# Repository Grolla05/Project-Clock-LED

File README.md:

# ⏱️ Project Clock LED — Digital Clock with Logic Circuits

> A fully functional digital clock built **without programming**, using only digital logic and discrete electronics.

---

## 🧩 What is DigitalClock?

**DigitalClock** is a project developed with the goal of creating a **complete digital clock** capable of accurately counting hours, minutes, and seconds using **only discrete electronic components and digital logic circuits**, **without any programming languages or microcontrollers**.

The project was designed to practically apply knowledge acquired in **Electronics** and **Digital Circuits** courses, resulting in a system capable of operating continuously and stably, displaying the time in real-time on **seven-segment LED displays**.

---

## 🎯 Project Objectives

- ⚡ Design and implement a **rectifier power supply** with proper filtering to power the digital circuits  
- ⏳ Develop a **clock generation system** using **delay and frequency divider circuits**  
- 🔁 Create **synchronous and asynchronous counters** using D flip-flops to count seconds, minutes, and hours  
- 🔢 Integrate **binary to 7-segment decoders** with the counters to correctly display the time values  

---

## ⚙️ Features

✔️ Accurate time counting (hours, minutes, and seconds)  
✔️ Continuous and stable real-time operation  
✔️ Real-time updates on seven-segment displays  
✔️ Fully built with discrete digital logic components  
✔️ No programming or microcontrollers involved  
✔️ Educational project focused on fundamental electronics

---

## 🛠️ Components and Technologies

- **D-type Flip-Flops**  
- **Synchronous/Asynchronous Counters**
- **Pulse Generator (CLOCK)** 
- **Frequency Dividers**  
- **BCD to 7-Segment Decoders**  
- **7-Segment LED Displays**
- **Diode LED's**
- **Rectifier Power Supply with Filter Capacitors**  
- **Logic Gates (AND, NOT, etc...)**

---

## ✨ System Demonstration

 <br>

---

## 👥 Author's

Developed by:

- **Felipe Grolla Freitas** – Control and Automation Engineering Student (PUC-Campinas)
- **Guilherme Oliveira Nogueira** - Control and Automation Engineering Student (PUC-Campinas)
- **Giovanna Lima Salvagnini** - Control and Automation Engineering Student (PUC-Campinas)
- **Henrique Spadaccia Chambó** - Control and Automation Engineering Student (PUC-Campinas)

---

## 💬 Contributions and Learning

This project demonstrated how to build a fully functional digital system using only the fundamentals of sequential and combinational logic.  
It reinforced practical understanding of counters, timing, clock generation, and display interfacing without any programming.

---

> 🧠 *"Digital logic can build time — one pulse at a time."*

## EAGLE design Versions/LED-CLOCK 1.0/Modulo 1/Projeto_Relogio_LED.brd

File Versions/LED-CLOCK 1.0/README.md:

## First version of the project (CLOCK LED with only analog and logic circuit)

## First version of the project in proteus

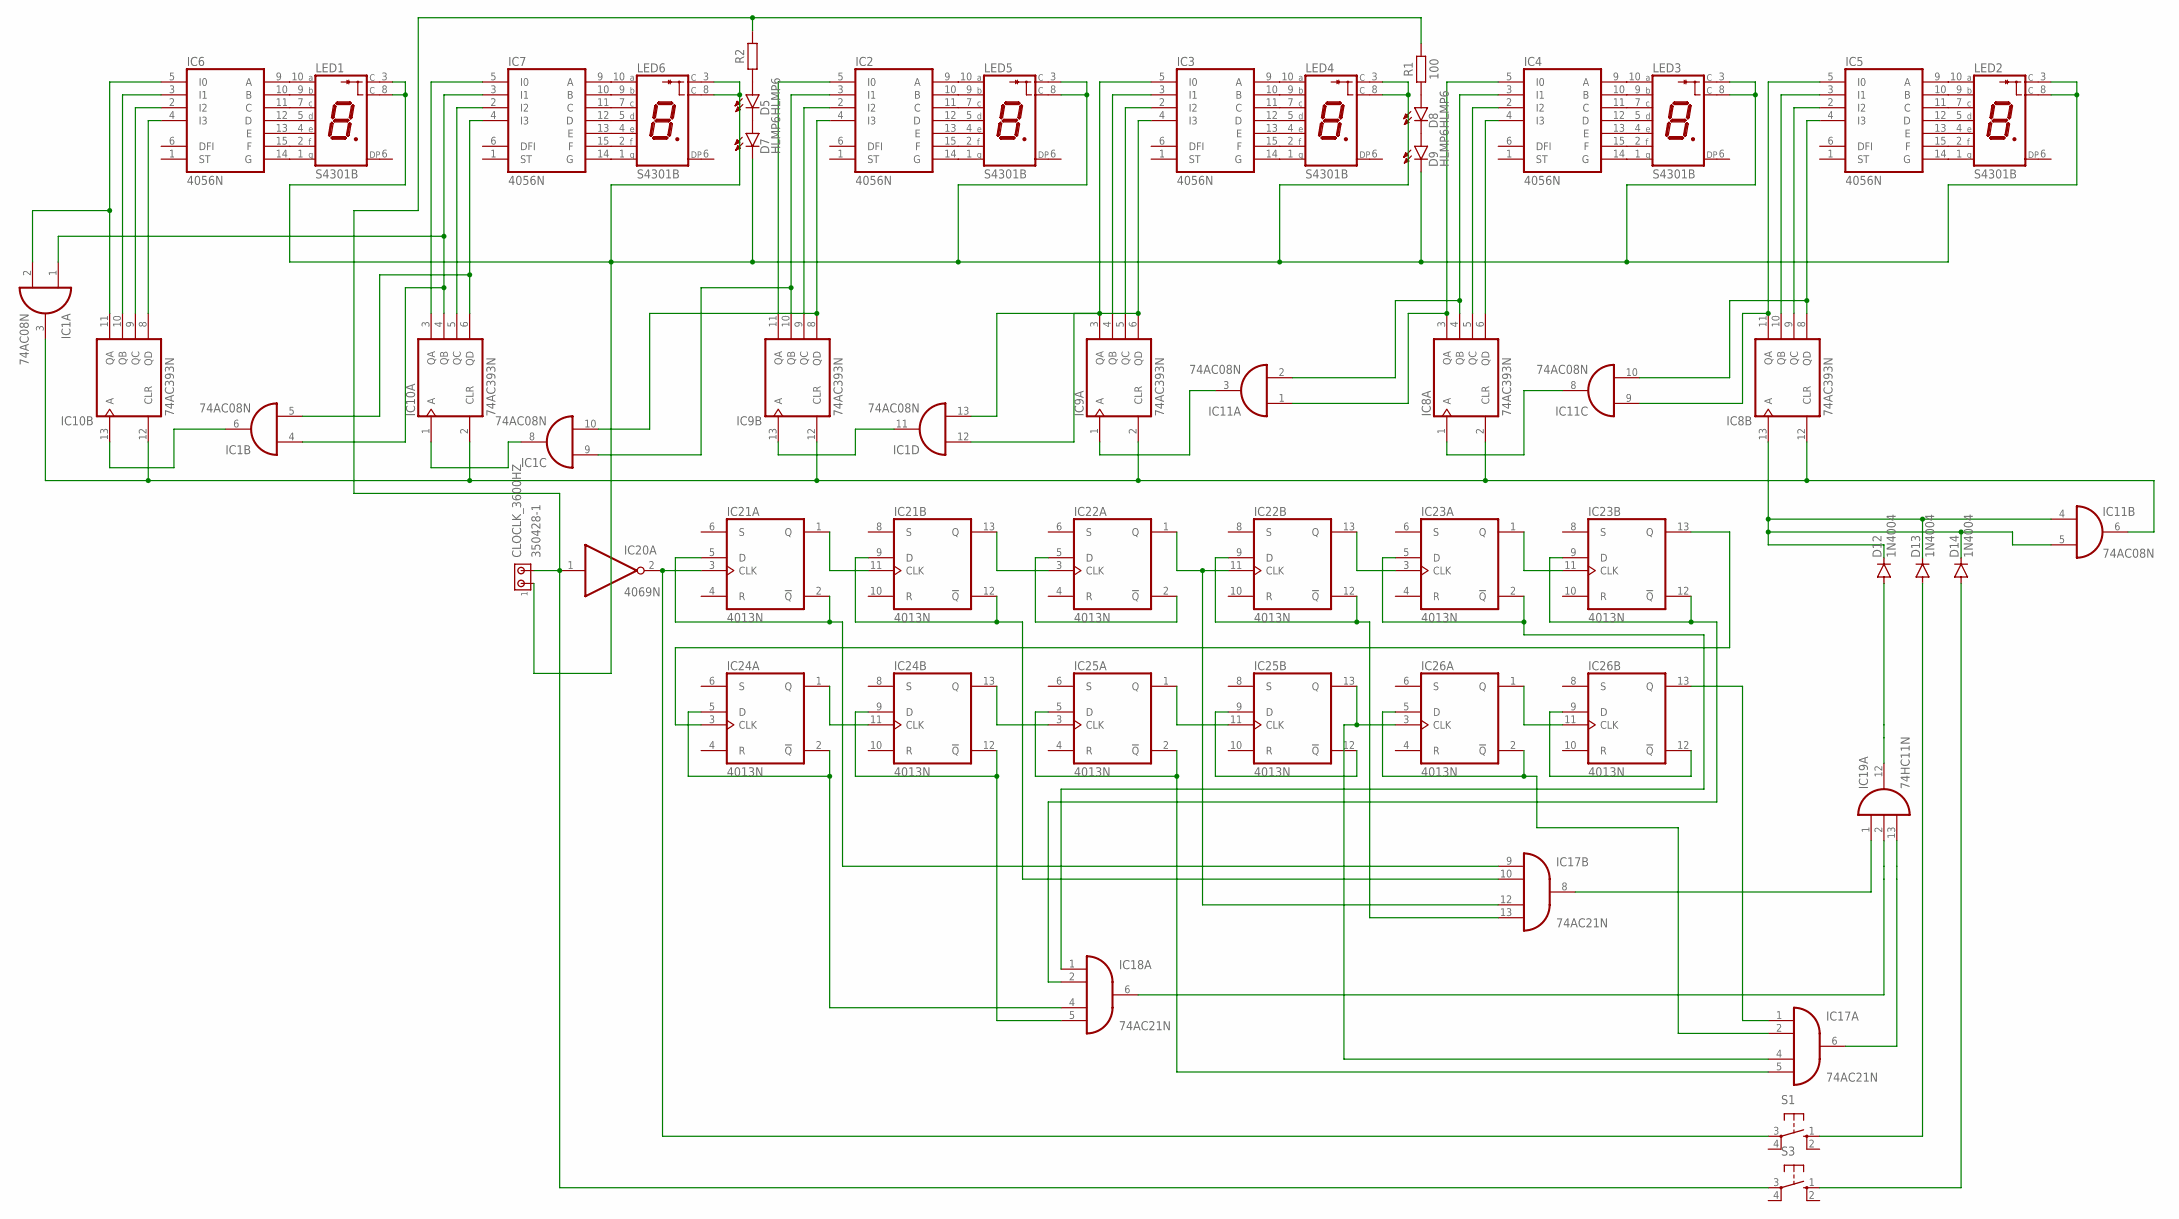
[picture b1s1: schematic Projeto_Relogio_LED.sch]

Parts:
CLOCLK_3600HZ: 350428-1
D5, D7, D8, D9: HLMP6
D12, D13, D14: 1N4004; DO41-10
IC1, IC11: 74AC08N; DIL14
IC2, IC3, IC4, IC5, IC6, IC7: 4056N; DIL16
IC8, IC9, IC10: 74AC393N; DIL14
IC17, IC18: 74AC21N; DIL14
IC19: 74HC11N; DIL14
IC20: 4069N; DIL14
IC21, IC22, IC23, IC24, IC25, IC26: 4013N; DIL14
LED1, LED2, LED3, LED4, LED5, LED6: S4301B
R1, R2: 100; RESAD1016W63L850D250B
S1, S3: 10-XX; B3F-10XX

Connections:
GND: IC1.7 (GND), IC2.8 (GND), IC3.8 (GND), IC4.8 (GND), IC5.8 (GND), IC6.8 (GND), IC7.8 (GND), IC8.7 (GND), IC9.7 (GND), IC10.7 (GND), IC11.7 (GND), IC17.7 (GND), IC18.7 (GND), IC19.7 (GND)
unnamed: IC1.8 (O), IC10.1 (A)
unnamed: IC5.4 (I3), IC8.8 (QD), IC11.10 (I1)
unnamed: IC8.1 (A), IC11.8 (O)
unnamed: D5.A, R2.1
unnamed: D8.A, R1.1
unnamed: D12.A, IC19.12 (O)
unnamed: IC20.2 (O), IC21.3 (CLK), S1.3
unnamed: IC21.1 (Q), IC21.11 (CLK)
unnamed: CLOCLK_3600HZ.2, IC20.1 (I), R1.2, R2.2, S3.3
unnamed: IC21.13 (Q), IC22.3 (CLK)
unnamed: IC17.12 (I2), IC22.1 (Q), IC22.11 (CLK)
unnamed: IC22.13 (Q), IC23.3 (CLK)
unnamed: IC23.1 (Q), IC23.11 (CLK)
unnamed: IC24.1 (Q), IC24.11 (CLK)
unnamed: IC18.4 (I2), IC24.2 (!Q), IC24.5 (D)
unnamed: IC24.13 (Q), IC25.3 (CLK)
unnamed: IC25.1 (Q), IC25.11 (CLK)
unnamed: IC17.4 (I2), IC25.13 (Q), IC26.3 (CLK)
unnamed: IC26.1 (Q), IC26.11 (CLK)
unnamed: IC23.13 (Q), IC24.3 (CLK)
unnamed: IC7.14 (G), LED6.1 (G)
unnamed: IC7.15 (F), LED6.2 (F)
unnamed: IC7.13 (E), LED6.4 (E)
unnamed: IC7.12 (D), LED6.5 (D)
unnamed: IC7.11 (C), LED6.7 (C)
unnamed: IC7.10 (B), LED6.9 (B)
unnamed: IC7.9 (A), LED6.10 (A)
unnamed: IC6.9 (A), LED1.10 (A)
unnamed: IC6.10 (B), LED1.9 (B)
unnamed: IC6.11 (C), LED1.7 (C)
unnamed: IC6.12 (D), LED1.5 (D)
unnamed: IC6.13 (E), LED1.4 (E)
unnamed: IC6.15 (F), LED1.2 (F)
unnamed: IC6.14 (G), LED1.1 (G)
unnamed: IC2.14 (G), LED5.1 (G)
unnamed: IC2.15 (F), LED5.2 (F)
unnamed: IC2.13 (E), LED5.4 (E)
unnamed: IC2.12 (D), LED5.5 (D)
unnamed: IC2.11 (C), LED5.7 (C)
unnamed: IC2.10 (B), LED5.9 (B)
unnamed: IC2.9 (A), LED5.10 (A)
unnamed: IC3.9 (A), LED4.10 (A)
unnamed: IC3.10 (B), LED4.9 (B)
unnamed: IC3.11 (C), LED4.7 (C)
unnamed: IC3.12 (D), LED4.5 (D)
unnamed: IC3.13 (E), LED4.4 (E)
unnamed: IC3.15 (F), LED4.2 (F)
unnamed: IC3.14 (G), LED4.1 (G)
unnamed: IC4.14 (G), LED3.1 (G)
unnamed: IC4.15 (F), LED3.2 (F)
unnamed: IC4.13 (E), LED3.4 (E)
unnamed: IC4.12 (D), LED3.5 (D)
unnamed: IC4.11 (C), LED3.7 (C)
unnamed: IC4.10 (B), LED3.9 (B)
unnamed: IC4.9 (A), LED3.10 (A)
unnamed: IC5.14 (G), LED2.1 (G)
unnamed: IC5.15 (F), LED2.2 (F)
unnamed: IC5.13 (E), LED2.4 (E)
unnamed: IC5.12 (D), LED2.5 (D)
unnamed: IC5.11 (C), LED2.7 (C)
unnamed: IC5.10 (B), LED2.9 (B)
unnamed: IC5.9 (A), LED2.10 (A)
unnamed: IC4.4 (I3), IC8.6 (QD)
unnamed: IC4.2 (I2), IC8.5 (QC)
unnamed: IC4.3 (I1), IC8.4 (QB), IC11.2 (I1)
unnamed: IC4.5 (I0), IC8.3 (QA), IC11.1 (I0)
unnamed: IC5.2 (I2), IC8.9 (QC)
unnamed: IC5.3 (I1), IC8.10 (QB)
unnamed: IC5.5 (I0), IC8.11 (QA), IC11.9 (I0)
unnamed: IC1.13 (I1), IC3.4 (I3), IC9.6 (QD)
unnamed: IC3.2 (I2), IC9.5 (QC)
unnamed: IC3.3 (I1), IC9.4 (QB)
unnamed: IC1.12 (I0), IC3.5 (I0), IC9.3 (QA)
unnamed: IC1.10 (I1), IC2.4 (I3), IC9.8 (QD)
unnamed: IC2.2 (I2), IC9.9 (QC)
unnamed: IC1.9 (I0), IC2.3 (I1), IC9.10 (QB)
unnamed: IC2.5 (I0), IC9.11 (QA)
unnamed: IC1.5 (I1), IC7.4 (I3), IC10.6 (QD)
unnamed: IC7.2 (I2), IC10.5 (QC)
unnamed: IC1.1 (I0), IC1.4 (I0), IC7.3 (I1), IC10.4 (QB)
unnamed: IC7.5 (I0), IC10.3 (QA)
unnamed: IC6.4 (I3), IC10.8 (QD)
unnamed: IC6.2 (I2), IC10.9 (QC)
unnamed: IC6.3 (I1), IC10.10 (QB)
unnamed: IC1.2 (I1), IC6.5 (I0), IC10.11 (QA)
unnamed: D5.K, D7.A
unnamed: D8.K, D9.A
unnamed: IC17.10 (I1), IC21.9 (D), IC21.12 (!Q)
unnamed: IC22.2 (!Q), IC22.5 (D)
unnamed: IC17.13 (I3), IC22.9 (D), IC22.12 (!Q)
unnamed: IC1.6 (O), IC10.13 (A)
unnamed: IC18.1 (I0), IC23.2 (!Q), IC23.5 (D)
unnamed: IC18.2 (I1), IC23.9 (D), IC23.12 (!Q)
unnamed: IC18.5 (I3), IC24.9 (D), IC24.12 (!Q)
unnamed: IC17.5 (I3), IC25.2 (!Q), IC25.5 (D)
unnamed: IC25.9 (D), IC25.12 (!Q)
unnamed: IC26.9 (D), IC26.12 (!Q)
unnamed: IC17.9 (I0), IC21.2 (!Q), IC21.5 (D)
unnamed: D12.C, D13.C, D14.C, IC8.13 (A), IC11.4 (I0), IC11.5 (I1)
unnamed: IC17.8 (O), IC19.1 (I0)
unnamed: D13.A, S1.1 (S)
unnamed: D14.A, S3.1 (S)
unnamed: IC18.6 (O), IC19.2 (I1)
unnamed: IC1.3 (O), IC8.2 (CLR), IC8.12 (CLR), IC9.2 (CLR), IC9.12 (CLR), IC10.2 (CLR), IC10.12 (CLR), IC11.6 (O)
unnamed: IC17.1 (I0), IC26.13 (Q)
unnamed: CLOCLK_3600HZ.1, D7.K, D9.K, LED1.3 (C), LED1.8 (C), LED2.3 (C), LED2.8 (C), LED3.3 (C), LED3.8 (C), LED4.3 (C), LED4.8 (C), LED5.3 (C), LED5.8 (C), LED6.3 (C), LED6.8 (C)
unnamed: IC9.1 (A), IC11.3 (O)
unnamed: IC17.2 (I1), IC26.2 (!Q), IC26.5 (D)
unnamed: IC1.11 (O), IC9.13 (A)
unnamed: IC17.6 (O), IC19.13 (I2)
VCC: IC1.14 (VCC), IC2.16 (VCC), IC3.16 (VCC), IC4.16 (VCC), IC5.16 (VCC), IC6.16 (VCC), IC7.16 (VCC), IC8.14 (VCC), IC9.14 (VCC), IC10.14 (VCC), IC11.14 (VCC), IC17.14 (VCC), IC18.14 (VCC), IC19.14 (VCC)
VDD: IC20.14 (VDD), IC21.14 (VDD), IC22.14 (VDD), IC23.14 (VDD), IC24.14 (VDD), IC25.14 (VDD), IC26.14 (VDD)
VEE: IC2.7 (VEE), IC3.7 (VEE), IC4.7 (VEE), IC5.7 (VEE), IC6.7 (VEE), IC7.7 (VEE)
VSS: IC20.7 (VSS), IC21.7 (VSS), IC22.7 (VSS), IC23.7 (VSS), IC24.7 (VSS), IC25.7 (VSS), IC26.7 (VSS)

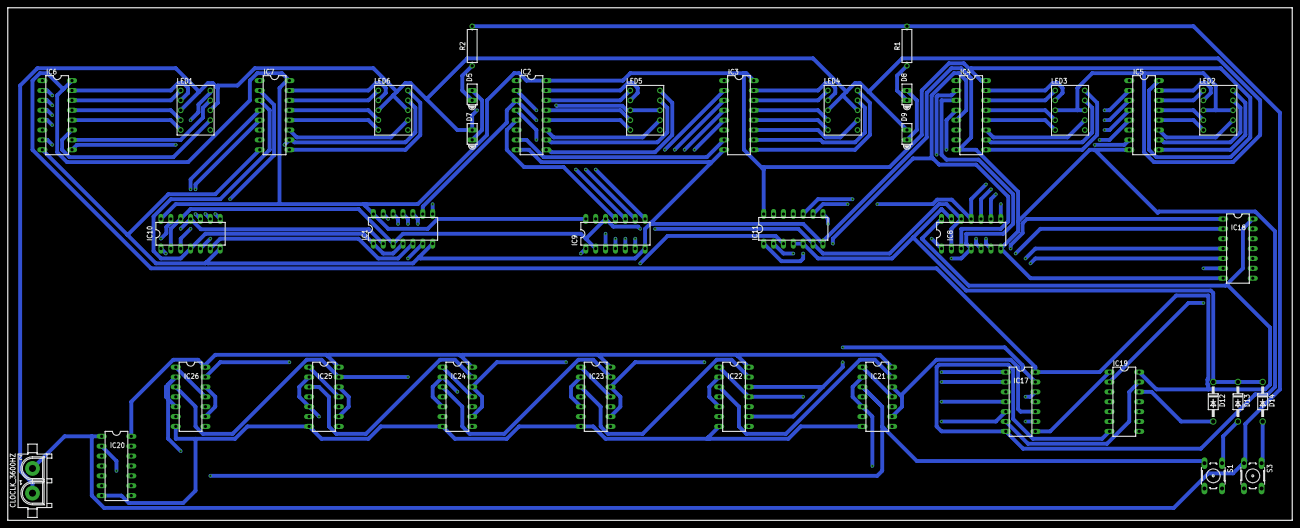
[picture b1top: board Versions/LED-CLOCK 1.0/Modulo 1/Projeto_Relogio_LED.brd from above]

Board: 2 copper layers, 330.2 x 131.8 mm, 39 parts (0 on the bottom side), 115 nets.

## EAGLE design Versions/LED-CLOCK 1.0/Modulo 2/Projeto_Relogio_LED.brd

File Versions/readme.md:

# Materials list

- **6 - 7 seg display**
- **6 - decodificador (7 segmentos display)**
- **6 - registradores de 4 bits**
- **4 - leds simples**
- **7 - Portas ands simples**
- **1 - porta and de 3 entradas**
- **3 - porta and de 4 entradas**
- **2 - botões (chave)**
- **12 - flipflops tipo D**
- **1 - porta not**
- **7 - diodos retificadores**
- **1 - oscilador NE555**
- **1 - resistor 1K**
- **1 - transistor NPN BD135**
- **1 - capacitor 220 uF**
- **1 - Zener 1N4728**
- **1 - transformador de 127v para 6v**

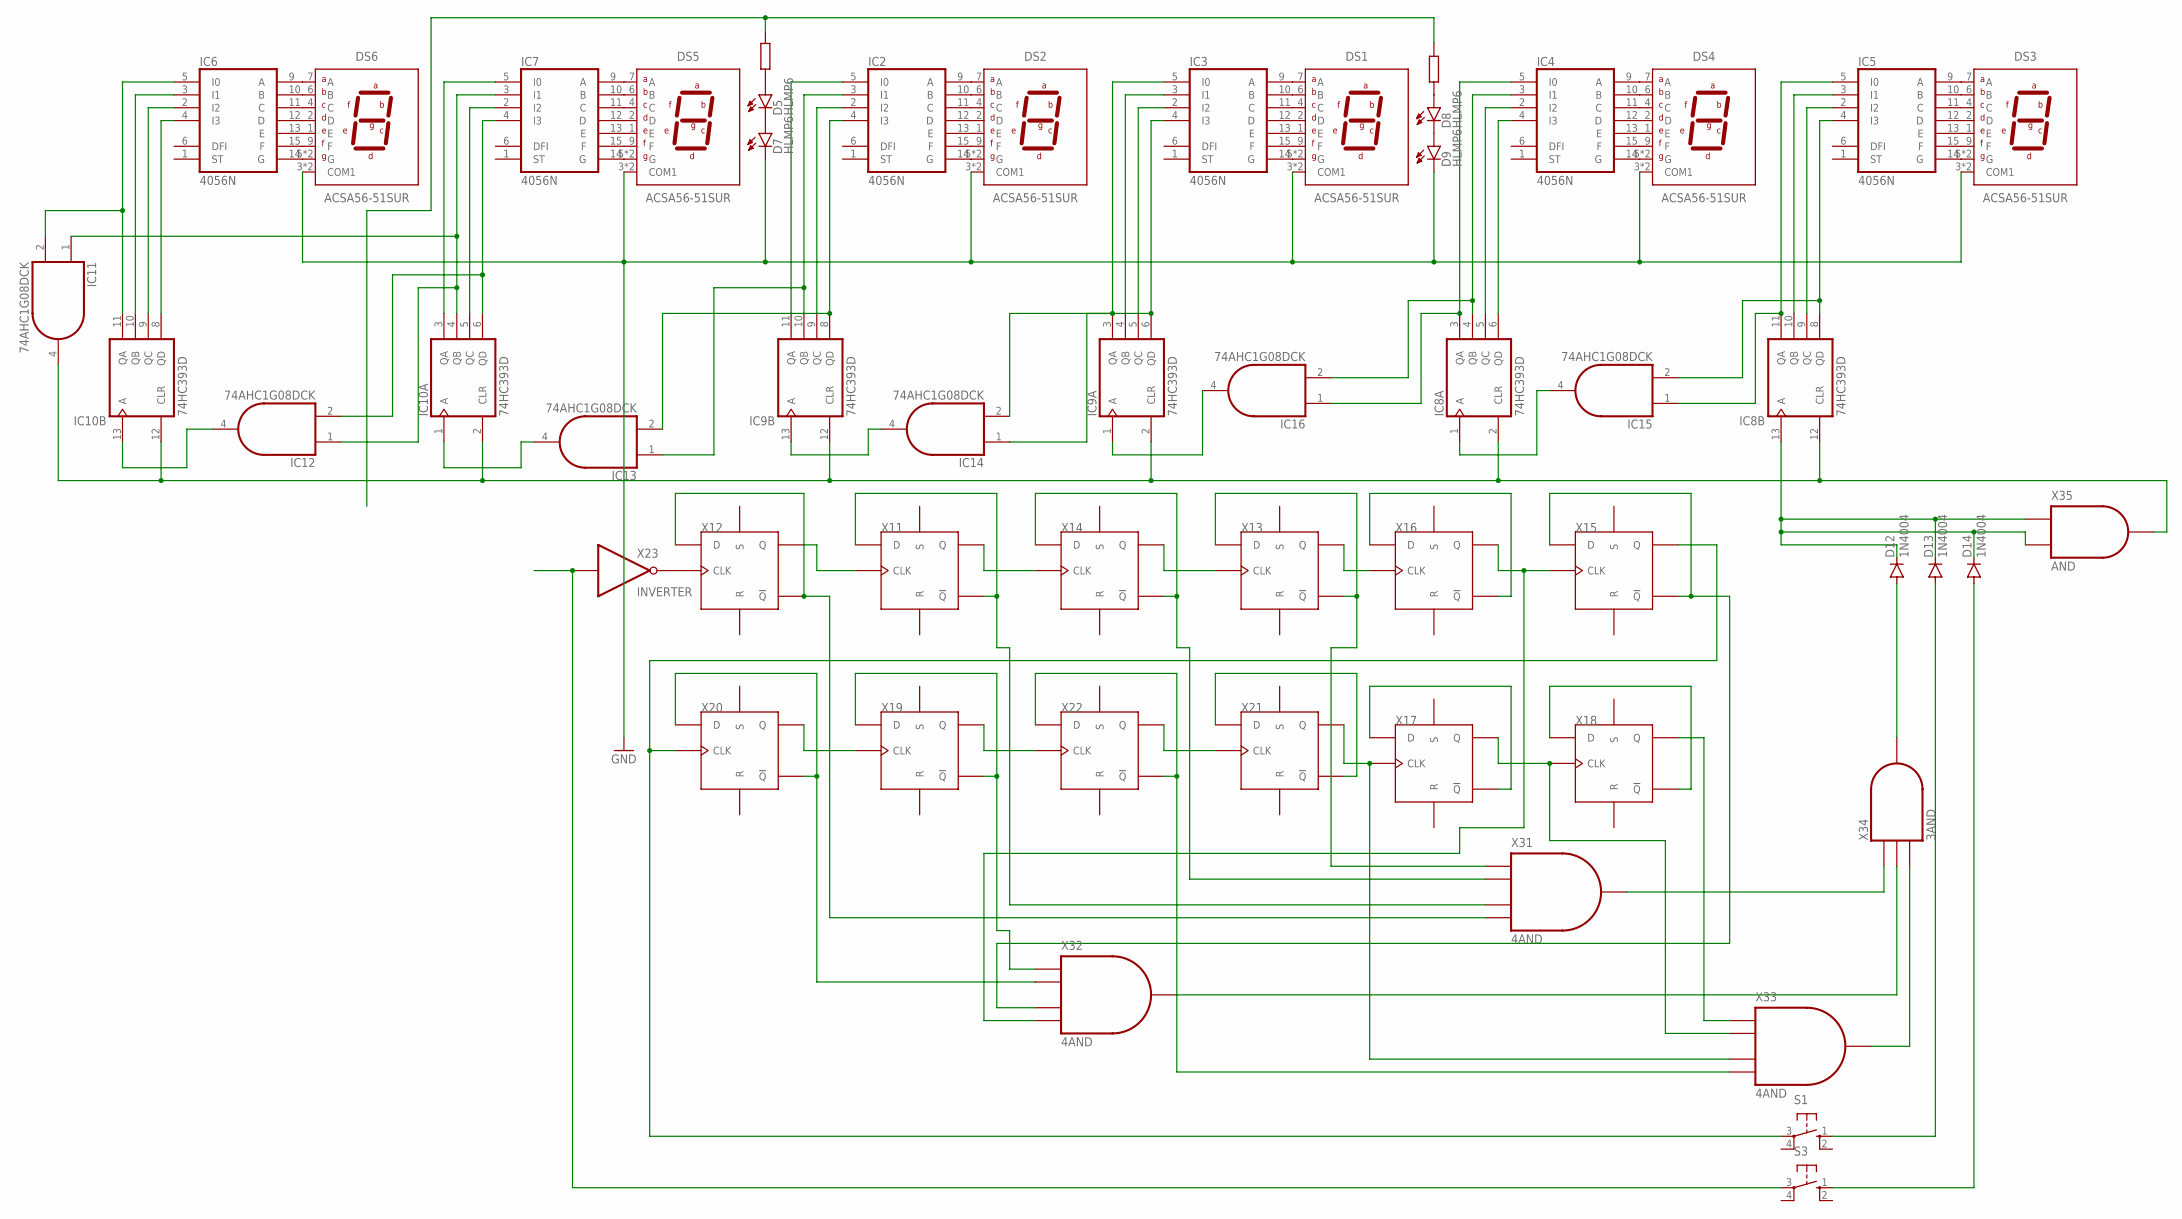
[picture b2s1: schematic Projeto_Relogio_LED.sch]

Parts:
D5, D7, D8, D9: HLMP6
D12, D13, D14: 1N4004; DO41-10
DS1, DS2, DS3, DS4, DS5, DS6: ACSA56-51SUR; ACSA56-51SURKWA
IC2, IC3, IC4, IC5, IC6, IC7: 4056N; DIL16
IC8, IC9, IC10: 74HC393D; SO14
IC11, IC12, IC13, IC14, IC15, IC16: 74AHC1G08DCK; SC70-5
S1, S3: 10-XX; B3F-10XX

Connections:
GND: D7.K, D9.K, DS1.3 (COM1), DS1.8 (COM1), DS2.3 (COM1), DS2.8 (COM1), DS3.3 (COM1), DS3.8 (COM1), DS4.3 (COM1), DS4.8 (COM1), DS5.3 (COM1), DS5.8 (COM1), DS6.3 (COM1), DS6.8 (COM1), IC2.8 (GND), IC3.8 (GND), IC4.8 (GND), IC5.8 (GND), IC6.8 (GND), IC7.8 (GND), IC8.7 (GND), IC9.7 (GND), IC10.7 (GND), IC11.3 (GND), IC12.3 (GND), IC13.3 (GND), IC14.3 (GND), IC15.3 (GND), IC16.3 (GND)
unnamed: IC10.1 (A), IC13.4 (O)
unnamed: IC5.4 (I3), IC8.8 (QD), IC15.2 (I1)
unnamed: IC8.1 (A), IC15.4 (O)
unnamed: DS5.7 (A), IC7.9 (A)
unnamed: DS5.6 (B), IC7.10 (B)
unnamed: DS5.4 (C), IC7.11 (C)
unnamed: DS5.2 (D), IC7.12 (D)
unnamed: DS5.1 (E), IC7.13 (E)
unnamed: DS5.5 (G), DS5.10 (G), IC7.14 (G)
unnamed: DS5.9 (F), IC7.15 (F)
unnamed: DS6.7 (A), IC6.9 (A)
unnamed: DS6.6 (B), IC6.10 (B)
unnamed: DS6.4 (C), IC6.11 (C)
unnamed: DS6.2 (D), IC6.12 (D)
unnamed: DS6.1 (E), IC6.13 (E)
unnamed: DS6.5 (G), DS6.10 (G), IC6.14 (G)
unnamed: DS6.9 (F), IC6.15 (F)
unnamed: DS3.7 (A), IC5.9 (A)
unnamed: DS3.6 (B), IC5.10 (B)
unnamed: DS3.4 (C), IC5.11 (C)
unnamed: DS3.2 (D), IC5.12 (D)
unnamed: DS3.1 (E), IC5.13 (E)
unnamed: DS3.5 (G), DS3.10 (G), IC5.14 (G)
unnamed: DS3.9 (F), IC5.15 (F)
unnamed: DS4.7 (A), IC4.9 (A)
unnamed: DS4.6 (B), IC4.10 (B)
unnamed: DS4.4 (C), IC4.11 (C)
unnamed: DS4.2 (D), IC4.12 (D)
unnamed: DS4.1 (E), IC4.13 (E)
unnamed: DS4.5 (G), DS4.10 (G), IC4.14 (G)
unnamed: DS4.9 (F), IC4.15 (F)
unnamed: DS1.7 (A), IC3.9 (A)
unnamed: DS1.6 (B), IC3.10 (B)
unnamed: DS1.4 (C), IC3.11 (C)
unnamed: DS1.2 (D), IC3.12 (D)
unnamed: DS1.1 (E), IC3.13 (E)
unnamed: DS1.5 (G), DS1.10 (G), IC3.14 (G)
unnamed: DS1.9 (F), IC3.15 (F)
unnamed: DS2.7 (A), IC2.9 (A)
unnamed: DS2.6 (B), IC2.10 (B)
unnamed: DS2.4 (C), IC2.11 (C)
unnamed: DS2.2 (D), IC2.12 (D)
unnamed: DS2.1 (E), IC2.13 (E)
unnamed: DS2.5 (G), DS2.10 (G), IC2.14 (G)
unnamed: DS2.9 (F), IC2.15 (F)
unnamed: IC4.4 (I3), IC8.6 (QD)
unnamed: IC4.2 (I2), IC8.5 (QC)
unnamed: IC4.3 (I1), IC8.4 (QB), IC16.2 (I1)
unnamed: IC4.5 (I0), IC8.3 (QA), IC16.1 (I0)
unnamed: IC5.2 (I2), IC8.9 (QC)
unnamed: IC5.3 (I1), IC8.10 (QB)
unnamed: IC5.5 (I0), IC8.11 (QA), IC15.1 (I0)
unnamed: IC3.4 (I3), IC9.6 (QD), IC14.2 (I1)
unnamed: IC3.2 (I2), IC9.5 (QC)
unnamed: IC3.3 (I1), IC9.4 (QB)
unnamed: IC3.5 (I0), IC9.3 (QA), IC14.1 (I0)
unnamed: IC2.4 (I3), IC9.8 (QD), IC13.2 (I1)
unnamed: IC2.2 (I2), IC9.9 (QC)
unnamed: IC2.3 (I1), IC9.10 (QB), IC13.1 (I0)
unnamed: IC2.5 (I0), IC9.11 (QA)
unnamed: IC7.4 (I3), IC10.6 (QD), IC12.2 (I1)
unnamed: IC7.2 (I2), IC10.5 (QC)
unnamed: IC7.3 (I1), IC10.4 (QB), IC11.1 (I0), IC12.1 (I0)
unnamed: IC7.5 (I0), IC10.3 (QA)
unnamed: IC6.4 (I3), IC10.8 (QD)
unnamed: IC6.2 (I2), IC10.9 (QC)
unnamed: IC6.3 (I1), IC10.10 (QB)
unnamed: IC6.5 (I0), IC10.11 (QA), IC11.2 (I1)
unnamed: D5.K, D7.A
unnamed: D8.K, D9.A
unnamed: IC10.13 (A), IC12.4 (O)
unnamed: D12.C, D13.C, D14.C, IC8.13 (A)
unnamed: D13.A, S1.1 (S)
unnamed: D14.A, S3.1 (S)
unnamed: IC8.2 (CLR), IC8.12 (CLR), IC9.2 (CLR), IC9.12 (CLR), IC10.2 (CLR), IC10.12 (CLR), IC11.4 (O)
unnamed: IC9.1 (A), IC16.4 (O)
unnamed: IC9.13 (A), IC14.4 (O)
VCC: IC2.16 (VCC), IC3.16 (VCC), IC4.16 (VCC), IC5.16 (VCC), IC6.16 (VCC), IC7.16 (VCC), IC8.14 (VCC), IC9.14 (VCC), IC10.14 (VCC), IC11.5 (VCC), IC12.5 (VCC), IC13.5 (VCC), IC14.5 (VCC), IC15.5 (VCC), IC16.5 (VCC)
VEE: IC2.7 (VEE), IC3.7 (VEE), IC4.7 (VEE), IC5.7 (VEE), IC6.7 (VEE), IC7.7 (VEE)

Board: 2 copper layers, 30 parts (0 on the bottom side), 80 nets, no tracks yet.

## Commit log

2025-05-10 Update versao 1.0 do circuito
2025-05-10 Rename image.png to First_version.png
2025-05-15 docs
2025-05-18 Update docs
2025-05-18 Rename image.png to Firs_version_Proteus.png
2025-05-21 docs update
2025-05-26 update
    Ultima versão para impressão na placa
2025-05-30 chore
